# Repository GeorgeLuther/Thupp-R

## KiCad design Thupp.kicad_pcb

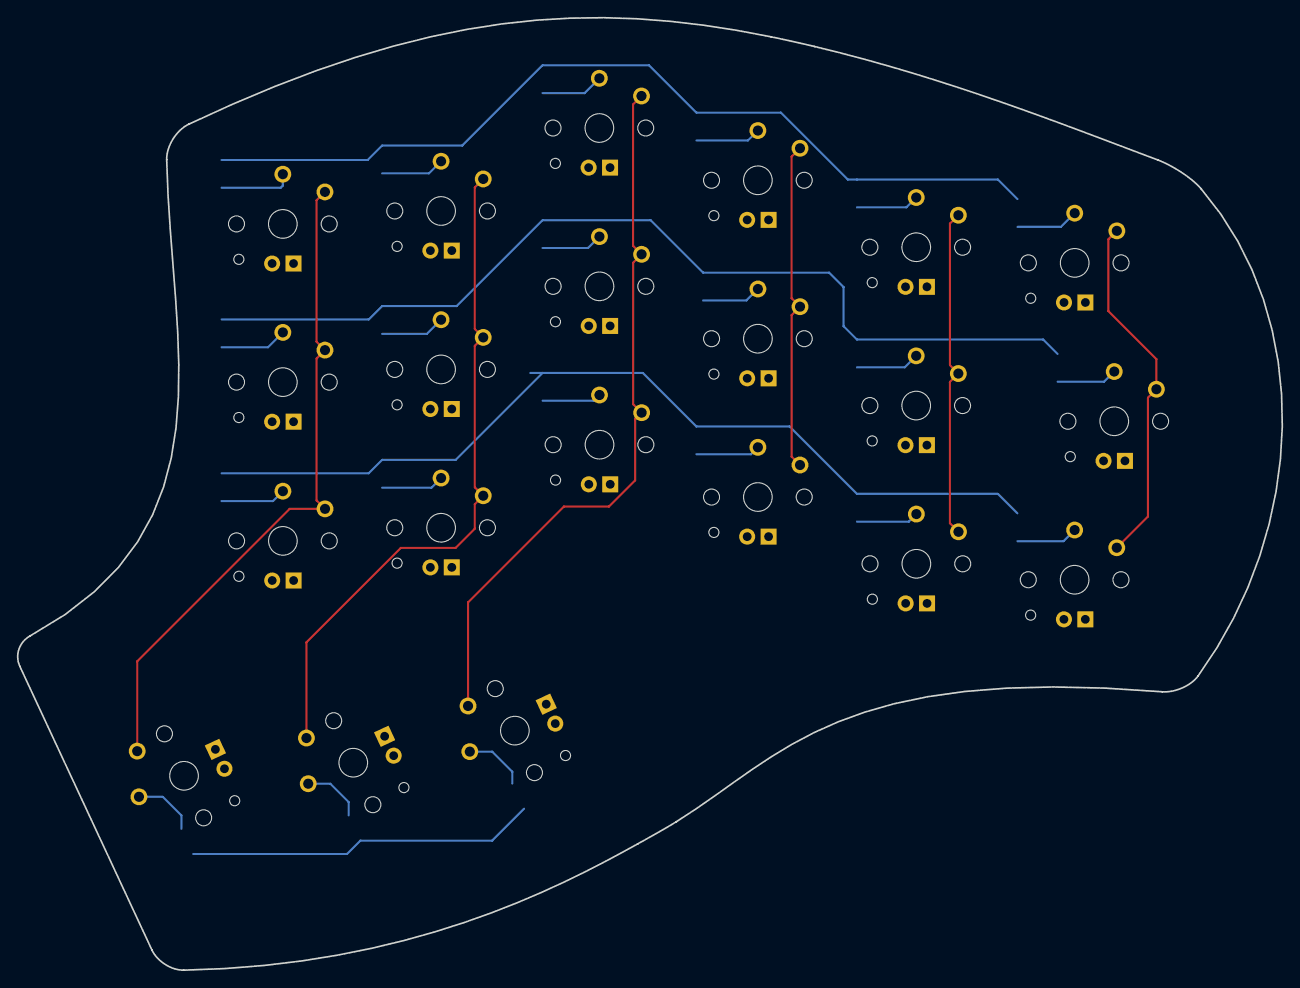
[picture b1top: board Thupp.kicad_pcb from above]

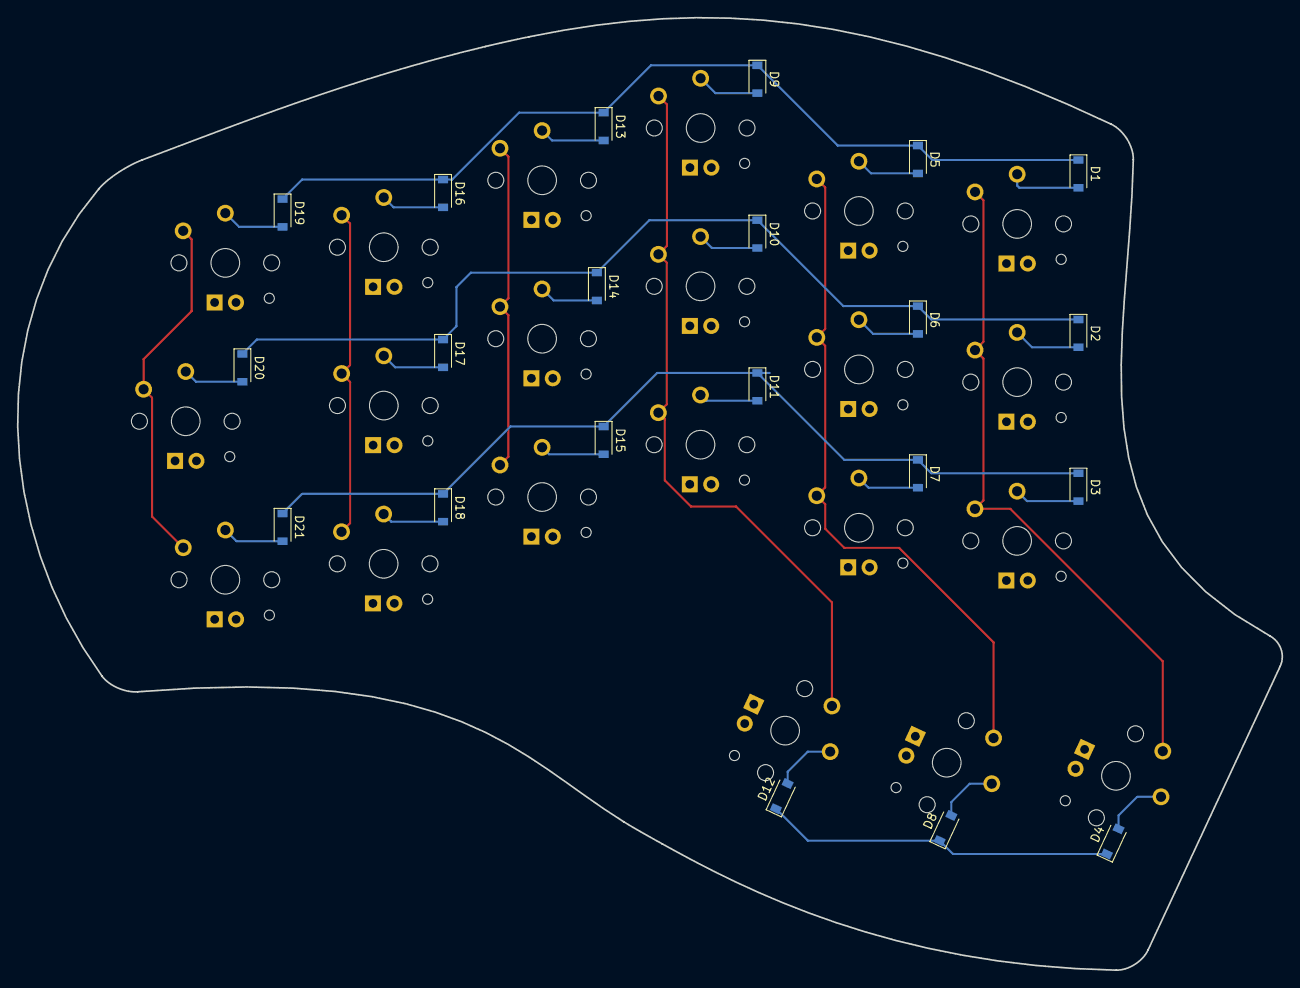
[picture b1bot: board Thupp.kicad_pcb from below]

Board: 2 copper layers, 150.1 x 113.0 mm, 42 parts (21 on the bottom side), 30 nets.

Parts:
D1, D2, D3, D4, D5, D6, D7, D8, D9, D10, D11, D12, D13, D14, D15, D16, D17, D18, D19, D20, D21: D_Small; D_SOD-123
MX1, MX2, MX3, MX5, MX6, MX7, MX9, MX10, MX11, MX13, MX14, MX15, MX16, MX17, MX18, MX19, MX21: MX-NoLED; KailhChoc-1U
MX4: MX-NoLED; KailhChoc-1.75U
MX8, MX12, MX20: MX-NoLED; KailhChoc-1.5U

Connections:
COL0: MX1.1, MX2.1, MX3.1, MX4.1
COL1: MX5.1, MX6.1, MX7.1, MX8.1
COL2: MX9.1, MX10.1, MX11.1, MX12.1
COL3: MX13.1, MX14.1, MX15.1
COL4: MX16.1, MX17.1, MX18.1
COL5: MX19.1, MX20.1, MX21.1
unnamed: D1.2, MX1.2
unnamed: D2.2, MX2.2
unnamed: D3.2, MX3.2
unnamed: D4.2, MX4.2
unnamed: D5.2, MX5.2
unnamed: D6.2, MX6.2
unnamed: D7.2, MX7.2
unnamed: D8.2, MX8.2
unnamed: D9.2, MX9.2
unnamed: D10.2, MX10.2
unnamed: D11.2, MX11.2
unnamed: D12.2, MX12.2
unnamed: D13.2, MX13.2
unnamed: D14.2, MX14.2
unnamed: D15.2, MX15.2
unnamed: D16.2, MX16.2
unnamed: D17.2, MX17.2
unnamed: D18.2, MX18.2
unnamed: D19.2, MX19.2
unnamed: D20.2, MX20.2
unnamed: D21.2, MX21.2
ROW0: D1.1, D5.1, D9.1, D13.1, D16.1, D19.1
ROW2: D2.1, D3.1, D6.1, D7.1, D10.1, D11.1, D14.1, D15.1, D17.1, D18.1, D20.1, D21.1
ROW3: D4.1, D8.1, D12.1

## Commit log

2021-10-10 add submodules
2021-10-10 added libs in kicad
2021-10-11 schematic finished, footprints assigned
2021-10-12 rough pcb footprint placement, imported svg as guide
2021-10-12 two layer pcb, diodes on bottom.. row based
2021-10-12 starting over for diodes on cols not rows
2021-10-16 most routing complete
2021-10-27 test-list
